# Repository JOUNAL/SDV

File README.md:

# SDV

# INTEGRANTES
<p>Santiago Quevedo Lopez</p>
<p>Juan Nicolas Torres Escobar</p>
<p>Juan Carlos Oliveros Garzón</p>

# DESCRIPCION DEL PROYECTO

<p>SDV es un dispositivo con el objetivo de defender objetos de valor que contenga dentro al detectar a alguien dentro de un rango disparando en este caso balas Nerf</p>

<h3>PROBLEMATICA</h3>
<p>SDV nace como la respuesta a la problematica de defender objetos de valor como por ejemplo en cajas de seguridad donde la unica barrera que protege a los obetos de valor es una barrera que muchas veces puede ser trasnpasada con facilidad</p>

<h3>ALCANCES</h3>
<p>Se esperea obtener una caja autodefendible cuando detecte aglo dentro de su rango de alcance</p>

<h3>OBJETIVOS</h3>
<ul>
<li>Hacer una caja que pueda disparar cuando detecte algo dentro de un rango propuesto dispare</li>
<li>Poder cambiar el rango de que tiene la caja para poder detectar una amenaza</li>
<li>Lanzar un sonido de advertencia cuando haya un objetivo en el rango propuesto</li>
<li>Prender leds parpadeantes cuando haya un objetivo dentro del rango propuesto</li>
</ul>

# DIAGRAMAS

<p>En este apartado de diagramas encontraremos el proceso grafico por el cual llevaremos a cabo nuestro objetivos propuesto</p>

<h3>DIAGRAMA DE FLUJO</h3>
<p>En este apartado encontraremos el proceso por el cual se lleva a cabo una accion, los procesos a los cuales llevara cabo esa accion y los resultados finales de esa accion</p>

<h3>DIAGRAMA DE CAJA NEGRA SIN TECNOLOGIA DEFINIDA</h3>
<p>En este apartado encontraremos encontraremos los procesos de entrada y salida con tecnologia ya aplicadpero sin especificar claramente cual es la que vamos a utilizar ya que se tiene que evaluar la caracteristica de cada componente para poder llevar a cabo los objetivos propuestos</p>

<h4>LISTA DE MATERIALES</h4>

<p>En este apartado encontraremos los materiales que usaremos parar completar el diagrama de caja negra y como se conectaran los diferentes componentes</p>

<p>Motores DC x2</p>
<p>Servomotor x1</p>
<p>Sensor ultrasonico x1</p>
<p>ESP 32 CAM x1</p>
<p>Leds x6</p>
<p>Buzzer x1</p>

<h3>DIAGRAMA DE CAJA NEGRA CON TECNOLOGIA DEFINIDA</h3>
<p>En este apartado encontraremos los procesos integrados en el diagrama anterior con los materiales seleccionados y como estos se llevarian a cabo</p>

# DISEÑOS

<p>1)En este primer diseño podremos apreciar como cada componente consume energia y asi poder calcular cuanta potencia requiere en total el circuito para poder funcionar</p>

<p>2)En este segundo diseño encontraremos la cantidad de pines que requeria cada componente para poder funcionar, esto con la finalidad de evaluar si teniamos la placa de programacion que necesitabamos</p>

# IMPLEMENTACION

<p>En esta seccion veremos como implementamos los componenetes para que cumplan la funcion designada</p>

<h3>ESQUEMATICO DEL CIRCUITO</h3>

<p>Este es el esquema circuital del  proyecto</p>

<h3>RUTEO PCB</h3>
<p>En esta parte podremos apreciar como se ruteo la PCB y como se dispusieron los diferentes elementos</p>

<p>Podremos apreciar que se decidio rutear por la parte de atras las conexiones principales y por delante se dispuso lo que seria el GND</p>

<h3>PCB 3D</h3>

# PRUEBAS

<p>1)En este caso de puso a prueba el SDV en un entorno controlado para comprobar su funcionalidad</p>
<p>https://youtu.be/dbPjX9YF6rE</p>

<p>2)En este caso se puso a prueba el SDV en una simulacion de lo que se encontraria cumpliendo a cabalidad su funcion, aumentado con este mismo fin la distancia que detectara el objetivo</p>
<p>https://youtu.be/GnnjFE5JcX4</p>

# CORTE
<p>En este ultimo apartado veremos el diseño que se utilizo para darle forma al SDV</p>

# CONCLUSONES
<p>Podemos dar por acabado este proyecto diciendo como resultado que llevar a cabo un proyecto es una trayectoria larga y algo dificil pero fructifera y que da un resultado satisfactorio cuando se observa el producto final</p>

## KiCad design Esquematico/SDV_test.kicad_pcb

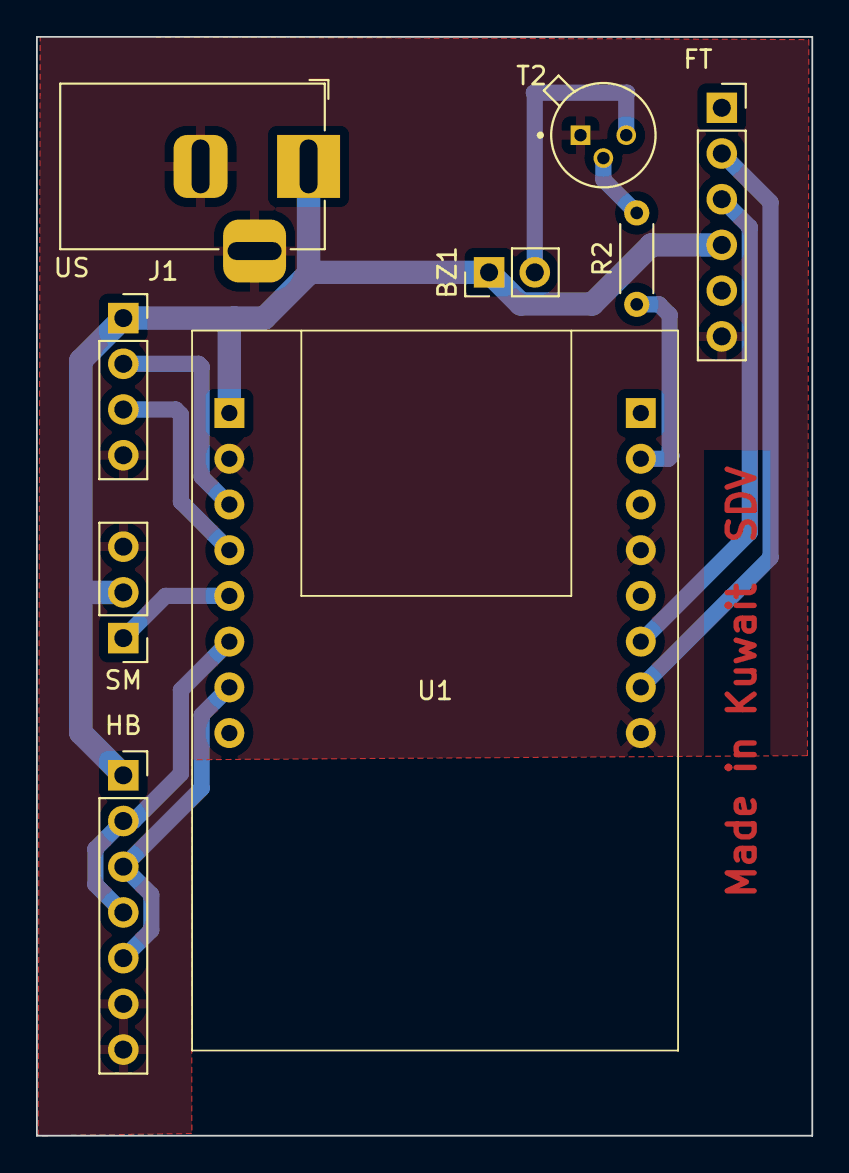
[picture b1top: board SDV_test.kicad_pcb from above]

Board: 2 copper layers, 43.1 x 61.0 mm, 9 parts (0 on the bottom side), 12 nets.

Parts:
BZ1: Buzzer; PinHeader_1x02_P2.54mm_Vertical
FT: 01x06Socket; PinSocket_1x06_P2.54mm_Vertical
HB: PinSocket_1x07_P2.54mm_Vertical
J1: Barrel_Jack_Switch; BarrelJack_Horizontal
R2: 1k; R_Axial_DIN0204_L3.6mm_D1.6mm_P5.08mm_Horizontal
SM: servo; PinHeader_1x03_P2.54mm_Vertical
T2: 2N2222; TO127P580H530-3
U1: ESP32-CAM
US: HC-SR04; PinSocket_1x04_P2.54mm_Vertical

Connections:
+5V: BZ1.1 (-), FT.4, HB.1 (5V), J1.1, SM.2 (VCC), U1.8 (5V), US.1 (VCC)
GND: FT.6, HB.6 (GND), HB.7 (GND), J1.2, J1.3, SM.3 (GND), T2.1, U1.7 (GND_1), U1.12 (GND_2), U1.16 (GND_3), US.4 (GND)
unnamed: BZ1.2 (+), T2.3
unnamed: FT.2, U1.15 (U0T)
unnamed: FT.3, U1.14 (U0R)
unnamed: R2.2, T2.2
unnamed: HB.3 (IN2), HB.5 (IN4), U1.2 (IO2)
unnamed: U1.6 (IO12), US.2 (TRIG)
unnamed: U1.5 (IO13), US.3 (ECHO)
unnamed: HB.2 (IN1), HB.4 (IN3), U1.3 (IO14)
unnamed: SM.1 (PWM), U1.4 (IO15)
unnamed: R2.1, U1.10 (IO16)

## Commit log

2023-06-24 Create Videos
2023-06-24 Update Videos
2023-06-25 Rename Videos to Enlaces/Videos
2023-06-27 Create Componentes
2023-06-27 Update Componentes
